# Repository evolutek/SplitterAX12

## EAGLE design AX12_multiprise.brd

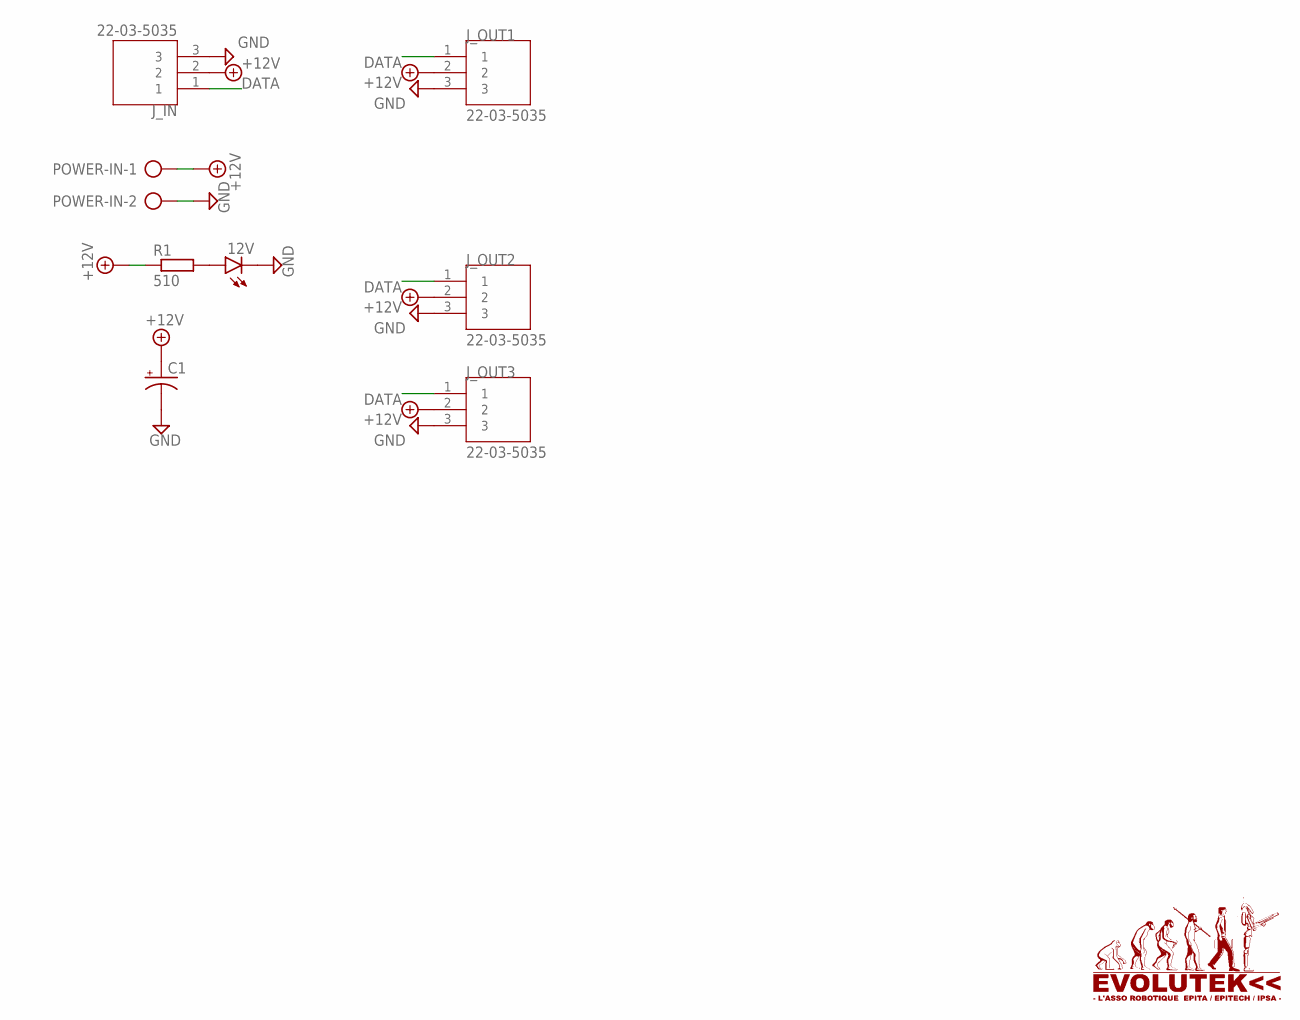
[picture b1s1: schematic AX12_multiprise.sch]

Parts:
12V: LEDCHIP-LED0805; CHIP-LED0805
C1: CPOL-USE5-10.5; E5-10,5
J_IN: 22-03-5035; MOLEX_22-03-5035
J_OUT1, J_OUT2, J_OUT3: 22-03-5035; MOLEX_22-03-5035
POWER-IN: AK500/2
R1: 510; R0603

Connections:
+12V: C1.+, J_IN.2, J_OUT1.2, J_OUT2.2, J_OUT3.2, POWER-IN.1, R1.1
DATA: J_IN.1, J_OUT1.1, J_OUT2.1, J_OUT3.1
GND: 12V.C, C1.-, J_IN.3, J_OUT1.3, J_OUT2.3, J_OUT3.3, POWER-IN.2
unnamed: 12V.A, R1.2

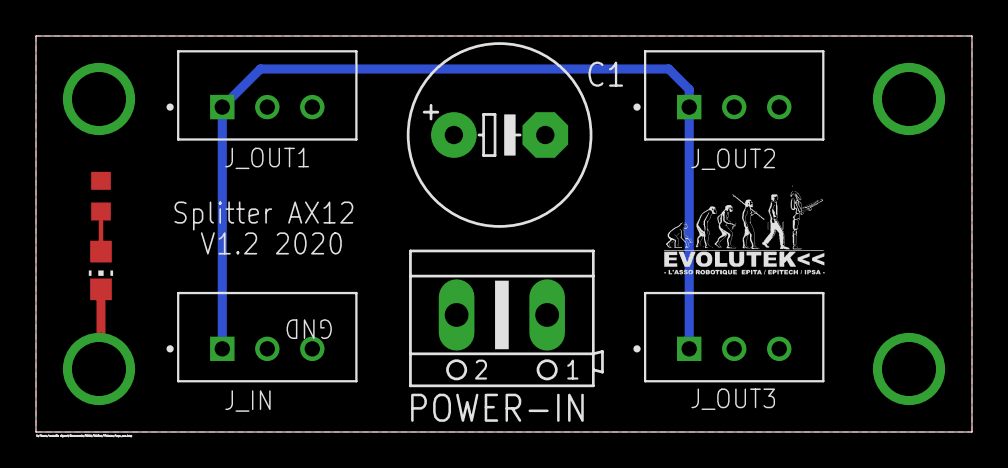
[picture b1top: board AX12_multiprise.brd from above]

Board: 2 copper layers, 52.0 x 22.0 mm, 8 parts (0 on the bottom side), 4 nets.

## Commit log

2020-01-22 First version complete
2020-01-22 Add gitignore
2020-01-22 Add step file for 22035035
2020-01-22 Change connector (the step is broken)
2020-01-22 Add library for 22-03-5035
2020-01-22 Update pdf
2020-01-24 Standarized resistance value and update pdf
2020-01-25 Add zip file for production
2020-01-25 [1.0] Correct the logo on the bottom
2020-09-03 [V1.2] Release V1.2
